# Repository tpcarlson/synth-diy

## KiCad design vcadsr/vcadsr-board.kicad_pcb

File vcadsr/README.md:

# VCADSR

##### What is this?

Voltage controlled ADSR, using the [ElectricDruid EnvGen8](https://electricdruid.net/product/envgen8/) chip. The module provides voltage control over most parameters (Attack, decay, sustain, release, time, level) as well as manual control with sliders. There are also three switches for toggling the mode, linear/exponential, and a fifth stage called "punch" which adds a little bit more to the attack on an envelope.

The mode toggle switch allows for gated looping, just looping (Almost like an LFO), and normal ADSR mode.

##### How much power does it use?

As measured by the joranalogue Test 3, around 40mA on +12v and 30mA on -12v at peak. The 5v rail is unused.

##### Where does the design come from?

The schematic is really an extension of the reference design on the [ElectricDruid](https://electricdruid.net/product/envgen8/) site, with some changes to add LEDs, and cutting features that would otherwise take up more panel space than I was comfortable with - I dropped the attenuators for CV inputs in favour of nice big manual controls with linear potentiometers instead.

##### Are there any rare/weird parts used?

You'll need one of the EnvGen8 chips in order to make this function at all!

##### Are there any problems with the design?

Just a couple, which are corrected in the version here. First, the LEDs for gate and trigger had some issues drawing too much power due to an oversight in the schematic. As it turns out LEDs don't really like being driven without a resistor! Second, the panel design had the mode and linear/exponential graphics switched which makes operating it a little bit more confusing than it otherwise ought to be.

These problems are both fixed in the repository right now though, however the fixes are *untested*. If I make another run of these boards, I will verify that the fix worked and remove this whole section!

##### Do you have a BOM/Mouser cart/Tayda links?

Sorry, no. Things go out of stock so frequently it'd be a lot of work to keep these up to date. Everything in this project is easy to source though, so you should not have any trouble.

##### Other resources

- [Assembly instructions](ASSEMBLY.md)
- [Interactive BOM](ibom.html) - This includes pre-soldered SMT parts as well as the through-hole parts. To use this, save the 'raw' view to your computer and open it in a web browser

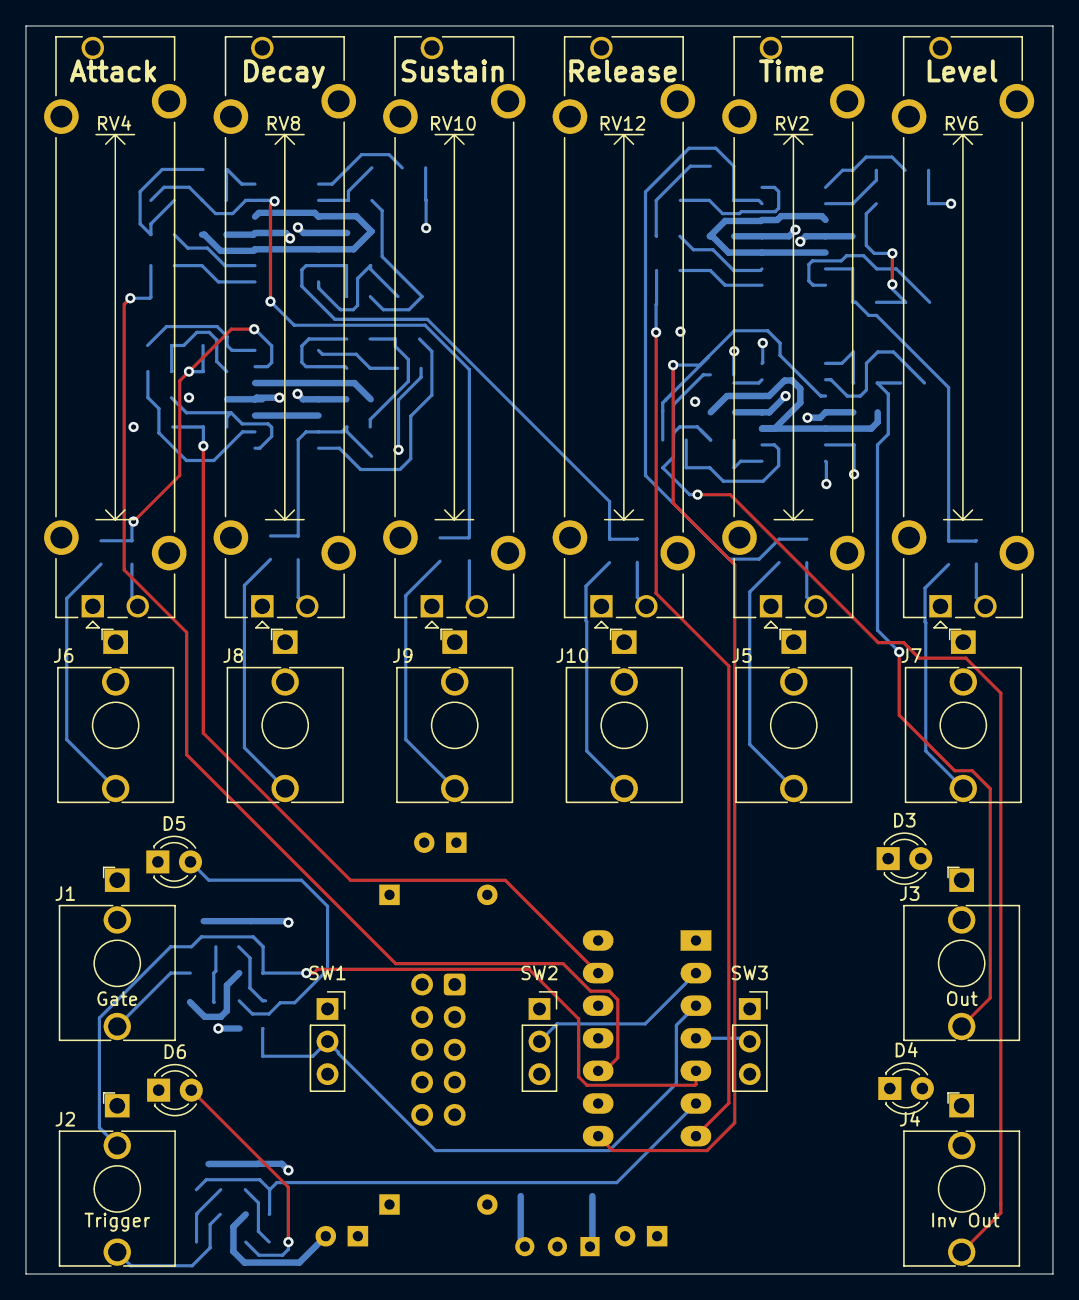
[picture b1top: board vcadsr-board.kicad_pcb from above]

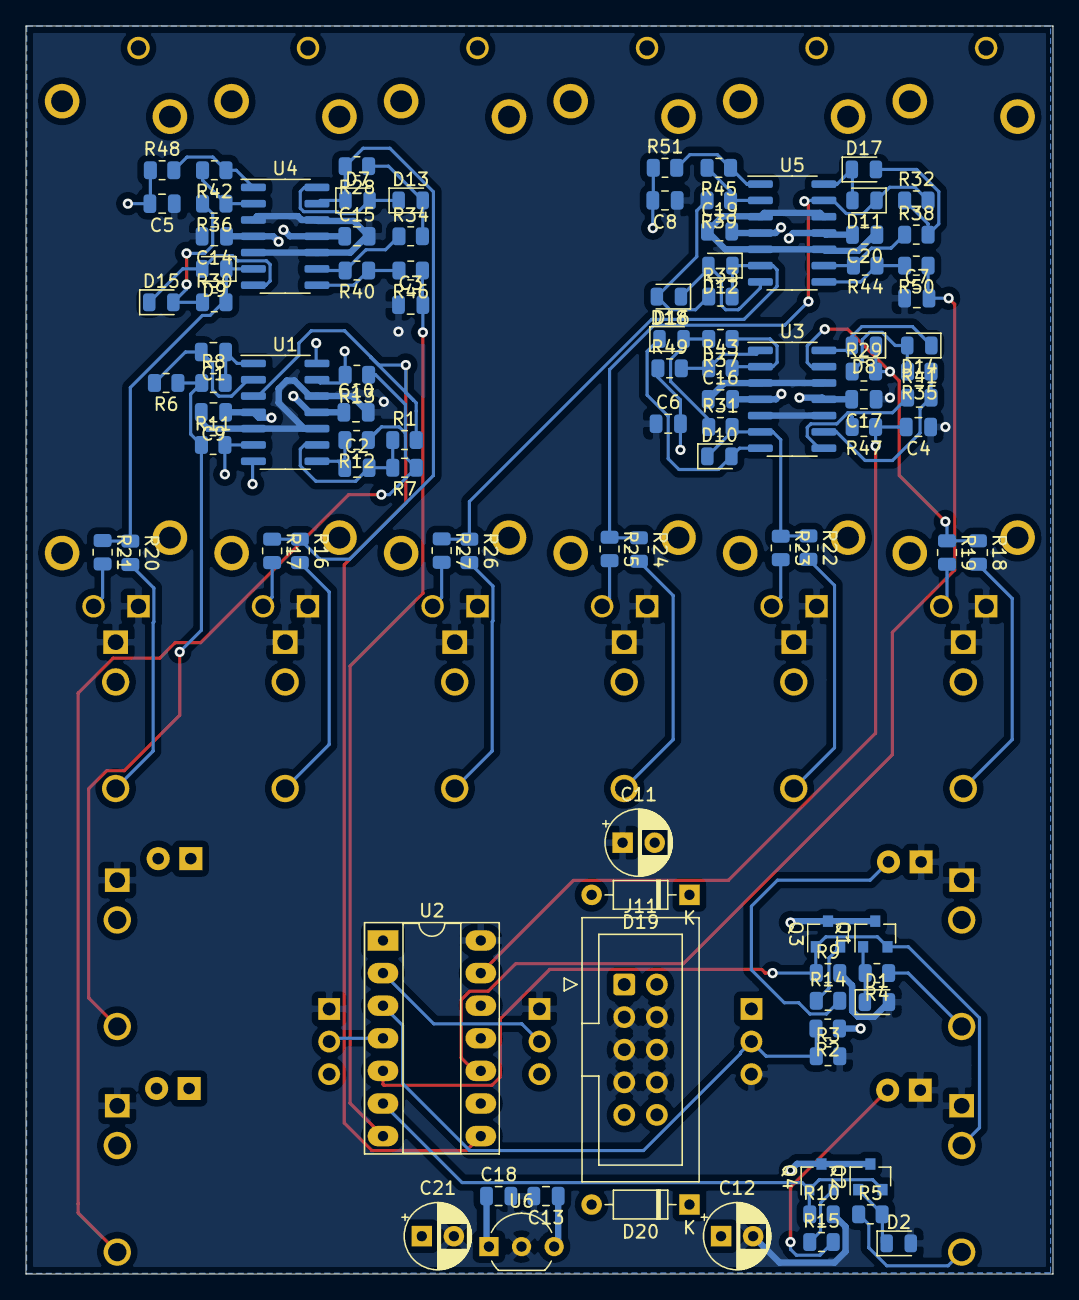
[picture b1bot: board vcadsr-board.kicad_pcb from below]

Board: 4 copper layers, 80.0 x 97.2 mm, 122 parts (99 on the bottom side), 78 nets.

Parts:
C1, C2: 1n; C_0805_2012Metric
C3, C4, C5, C6, C7, C8, C9, C10, C13, C14, C15, C16, C17, C18, C19, C20: 100n; C_0805_2012Metric
C11, C12, C21: 10u; CP_Radial_D5.0mm_P2.50mm
D1, D2, D7, D8, D9, D10, D11, D12, D13, D14, D15, D16, D17, D18: 1N4148; D_0805_2012Metric
D3, D4, D5, D6: LED; LED_D3.0mm
D19, D20: D_Schottky; D_DO-35_SOD27_P7.62mm_Horizontal
J1, J3, J4, J5, J6, J7, J8, J9, J10: AudioJack2; Jack_3.5mm_QingPu_WQP-PJ398SM_Vertical_CircularHoles
J2: AudioJack2_SwitchT; Jack_3.5mm_QingPu_WQP-PJ398SM_Vertical_CircularHoles
J11: Conn_02x05_Odd_Even; IDC-Header_2x05_P2.54mm_Vertical
Q1, Q2, Q3, Q4: MMBT3904; SOT-23
R1, R6, R7, R17, R19, R21, R23, R25, R27, R28, R29, R30, R31, R32, R33, R34, R35, R36, R37, R38, R39, R40, R41, R42, R43, R44, R45: 100k; R_0805_2012Metric
R2, R3, R4, R5, R9, R10: 10k; R_0805_2012Metric
R8, R12: 330; R_0805_2012Metric
R11, R13, R14, R15: 4.7k; R_0805_2012Metric
R16, R18, R20, R22, R24, R26: 200k; R_0805_2012Metric
R46, R47, R48, R49, R50, R51: 4k7; R_0805_2012Metric
RV2, RV4, RV6, RV8, RV10, RV12: 10k; Potentiometer_Bourns_PTA3043_Single_Slide
SW1: SW_SPDT_MSM; PinSocket_1x03_P2.54mm_Vertical
SW2, SW3: SW_SPST; PinSocket_1x03_P2.54mm_Vertical
U1, U3, U4, U5: TL074; SOIC-14_3.9x8.7mm_P1.27mm
U2: ENVGEN8; DIP-14_W7.62mm_Socket_LongPads
U6: L78L05_TO92; TO-92_Inline_Wide

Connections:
+5V: C18.1, C21.1, Q1.3, Q2.3, Q3.3, Q4.3, R2.1, RV2.3, RV4.3, RV6.3, RV8.3, RV10.3, RV12.3, SW1.1, U2.1, U6.1
+12V: C9.1, C12.1, C13.1, C14.1, C16.2, C19.2, D20.1, U1.4, U3.4, U4.4, U5.4, U6.3
-12V: C10.1, C11.2, C15.1, C17.2, C20.2, D19.2, U1.11, U3.11, U4.11, U5.11
/ATTACK: C4.2, R47.1, U2.13
/DECAY: C6.2, R49.1, U2.11
/LEVEL: C5.2, R48.1, U2.12
/RELEASE: C8.2, R51.1, U2.9
/SUSTAIN: C7.2, R50.1, U2.10
/TIME: C3.2, R46.1, U2.7
ENV_OUT: R1.2, U1.3, U2.8
Earth: C3.1, C4.1, C5.1, C6.1, C7.1, C8.1, C9.2, C10.2, C11.1, C12.2, C13.2, C14.2, C15.2, C16.1, C17.1, C18.2, C19.1, C20.1, C21.2, D1.2, D2.2, D5.1, D6.1, J1.S, J2.S, J3.S, J4.S, J5.S, J6.S, J7.S, J8.S, J9.S, J10.S, J11.3, J11.4, J11.5, J11.6, J11.7, J11.8, R3.2, R9.2, R10.2, RV2.1, RV4.1, RV6.1, RV8.1, RV10.1, RV12.1, SW1.3, SW2.1, SW3.1, U1.5, U1.10, U1.12, U2.14, U3.3, U3.5, U3.10, U3.12, U4.3, U4.5, U4.10, U4.12, U5.3, U5.5, U5.10, U5.12, U6.2
GATE: J2.TN, Q1.2, Q3.1, R9.1, U2.5
LINEAR: SW3.2, U2.4
MODE_CV: R2.2, R3.1, SW1.2, U2.3
unnamed: C1.1, R8.2, U1.1
unnamed: C1.2, R6.2, U1.2
unnamed: C2.1, R12.2, U1.8
unnamed: C2.2, R1.1, R7.2, U1.9
unnamed: D1.1, Q1.1, R4.2
unnamed: D2.1, Q2.1, R5.2
unnamed: D3.1, U1.7
unnamed: D3.2, R11.2, U1.6
unnamed: D4.1, R13.2, U1.13
unnamed: D4.2, U1.14
unnamed: D5.2, R14.2
unnamed: D6.2, R15.2
unnamed: D10.2, D16.1, U3.7
unnamed: D11.2, D17.1, U5.14
unnamed: D12.2, D18.1, U5.7
unnamed: D7.2, D13.1, U4.14
unnamed: D13.2, R28.1, R34.2
unnamed: D8.2, D14.1, U3.14
unnamed: D14.2, R29.1, R35.2
unnamed: D9.2, D15.1, U4.7
unnamed: D15.2, R30.1, R36.2
unnamed: D16.2, R31.1, R37.2
unnamed: D17.2, R32.1, R38.2
unnamed: D18.2, R33.1, R39.2
unnamed: D19.1, J11.1, J11.2
unnamed: D20.2, J11.9, J11.10
unnamed: J1.T, R4.1
unnamed: J2.T, R5.1
unnamed: J3.T, R6.1, R8.1, R11.1
unnamed: J4.T, R7.1, R12.1, R13.1
unnamed: J5.T, R16.2
unnamed: J6.T, R18.2
unnamed: J7.T, R20.2
unnamed: J8.T, R22.2
unnamed: J9.T, R24.2
unnamed: J10.T, R26.2
unnamed: Q3.2, R14.1
unnamed: Q4.2, R15.1
unnamed: R17.2, RV2.2
unnamed: R19.2, RV4.2
unnamed: R21.2, RV6.2
unnamed: R23.2, RV8.2
unnamed: R25.2, RV10.2
unnamed: R27.2, RV12.2
unnamed: R34.1, R40.2, U4.9
unnamed: R35.1, R41.2, U3.9
unnamed: R36.1, R42.2, U4.2
unnamed: R37.1, R43.2, U3.2
unnamed: R38.1, R44.2, U5.9
unnamed: R39.1, R45.2, U5.2
unnamed: R40.1, R46.2, U4.8
unnamed: R41.1, R47.2, U3.8
unnamed: R42.1, R48.2, U4.1
unnamed: R43.1, R49.2, U3.1
unnamed: R44.1, R50.2, U5.8
unnamed: R45.1, R51.2, U5.1
PUNCH: SW2.2, U2.2
TRIGGER: Q2.2, Q4.1, R10.1, U2.6
_ATTACK: D8.1, R18.1, R19.1, R29.2, U3.13
_DECAY: D10.1, R22.1, R23.1, R31.2, U3.6
_LEVEL: D9.1, R20.1, R21.1, R30.2, U4.6
_RELEASE: D12.1, R26.1, R27.1, R33.2, U5.6
_SUSTAIN: D11.1, R24.1, R25.1, R32.2, U5.13
_TIME: D7.1, R16.1, R17.1, R28.2, U4.13

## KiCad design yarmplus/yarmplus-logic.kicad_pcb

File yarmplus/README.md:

# YARM+

##### What is this?

An implementation of the [YARM+](https://www.schmitzbits.de/vca.html) ring modulator by René Schmitz.

##### How much power does it use?

As measured by the joranalogue Test 3, around 15mA on +12v and 10mA on -12v at peak. The 5v rail is unused.

##### Where does the design come from?

From the [VCA](https://www.schmitzbits.de/vca.html) pages of René Schmitz.

##### Are there any rare/weird parts used?

You'll need to find an MC1496P chip to build this, unfortunately they're a little difficult to track down. I got mine from Aliexpress and the chips that arrived appeared to be recycled from dead electronics. I'd usually try and buy new chips from proper retailers where possible...

##### Are there any problems with the design?

Nope, works nicely! If I were to add anything, perhaps indicator LEDs for the two inputs and the output - but I'm an LED junkie, and it's definitely not necessary.

##### Do you have a BOM/Mouser cart/Tayda links?

Sorry, no. Things go out of stock so frequently it'd be a lot of work to keep these up to date. Everything in this project is easy to source though (Other than the MC1496P), so you should not have any trouble.

##### Other resources

- [Assembly Instructions](ASSEMBLY.md)
- [Interactive BOM](ibom.html) - To use this, save the 'raw' view to your computer and open it in a web browser

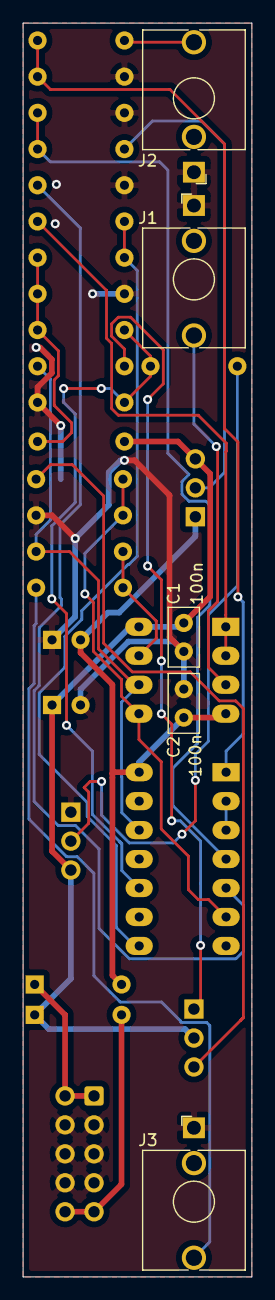
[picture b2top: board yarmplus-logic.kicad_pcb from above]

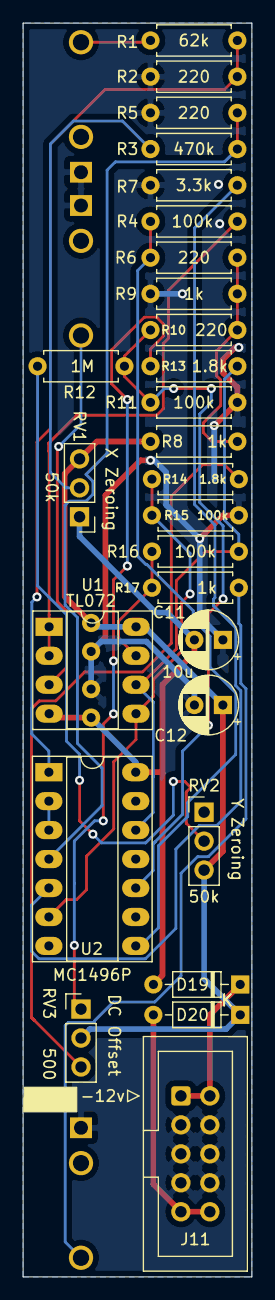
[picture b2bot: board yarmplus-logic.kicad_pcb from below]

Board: 2 copper layers, 20.1 x 110.0 mm, 32 parts (27 on the bottom side), 23 nets.

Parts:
C1, C2: 100n; C_Disc_D5.0mm_W2.5mm_P2.50mm
C11, C12: 10u; CP_Radial_D5.0mm_P2.50mm
D19, D20: D_Schottky; D_DO-35_SOD27_P7.62mm_Horizontal
J1, J2, J3: AudioJack2; Jack_3.5mm_QingPu_WQP-PJ398SM_Vertical_CircularHoles
J11: Conn_02x05_Odd_Even; IDC-Header_2x05_P2.54mm_Vertical
R1: 62k; R_Axial_DIN0207_L6.3mm_D2.5mm_P7.62mm_Horizontal
R2, R5, R6, R10: 220; R_Axial_DIN0207_L6.3mm_D2.5mm_P7.62mm_Horizontal
R3: 470k; R_Axial_DIN0207_L6.3mm_D2.5mm_P7.62mm_Horizontal
R4, R11, R15, R16: 100k; R_Axial_DIN0207_L6.3mm_D2.5mm_P7.62mm_Horizontal
R7: 3.3k; R_Axial_DIN0207_L6.3mm_D2.5mm_P7.62mm_Horizontal
R8, R9, R17: 1k; R_Axial_DIN0207_L6.3mm_D2.5mm_P7.62mm_Horizontal
R12: 1M; R_Axial_DIN0207_L6.3mm_D2.5mm_P7.62mm_Horizontal
R13, R14: 1.8k; R_Axial_DIN0207_L6.3mm_D2.5mm_P7.62mm_Horizontal
RV1, RV2: 50k; PinHeader_1x03_P2.54mm_Vertical
RV3: 500; PinHeader_1x03_P2.54mm_Vertical
U1: TL072; DIP-8_W7.62mm_Socket_LongPads
U2: MC1496P; DIP-14_W7.62mm_Socket_LongPads

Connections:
+12V: C1.2, C12.1, D20.1, R8.1, RV1.3, RV2.3, RV3.2, U1.8
-12V: C2.2, C11.2, D19.2, RV1.1, U1.4, U2.14
Earth: C1.1, C2.1, C11.1, C12.2, J1.S, J2.S, J3.S, J11.3, J11.4, J11.5, J11.6, J11.7, J11.8, R2.2, R5.2, R7.2, R9.2, R11.2, R15.2, RV2.1
unnamed: D19.1, J11.1, J11.2
unnamed: D20.2, J11.9, J11.10
unnamed: J1.T, U1.3
unnamed: J2.T, R1.2
unnamed: J3.T, R17.1
unnamed: R1.1, R2.1, U2.1
unnamed: R3.1, R5.1, U2.4
unnamed: R3.2, RV1.2
unnamed: R4.1, R6.2, U2.8
unnamed: R4.2, U1.1, U1.2
unnamed: R7.1, U2.5
unnamed: R10.1, R11.1, R12.2, U2.10
unnamed: R6.1, R8.2, R9.1, R10.2
unnamed: R12.1, RV2.2
unnamed: R13.1, RV3.1
unnamed: R13.2, R16.2, U1.6, U2.12
unnamed: R14.1, RV3.3
unnamed: R14.2, R15.1, U1.5, U2.6
unnamed: R16.1, R17.2, U1.7
unnamed: U2.2, U2.3
